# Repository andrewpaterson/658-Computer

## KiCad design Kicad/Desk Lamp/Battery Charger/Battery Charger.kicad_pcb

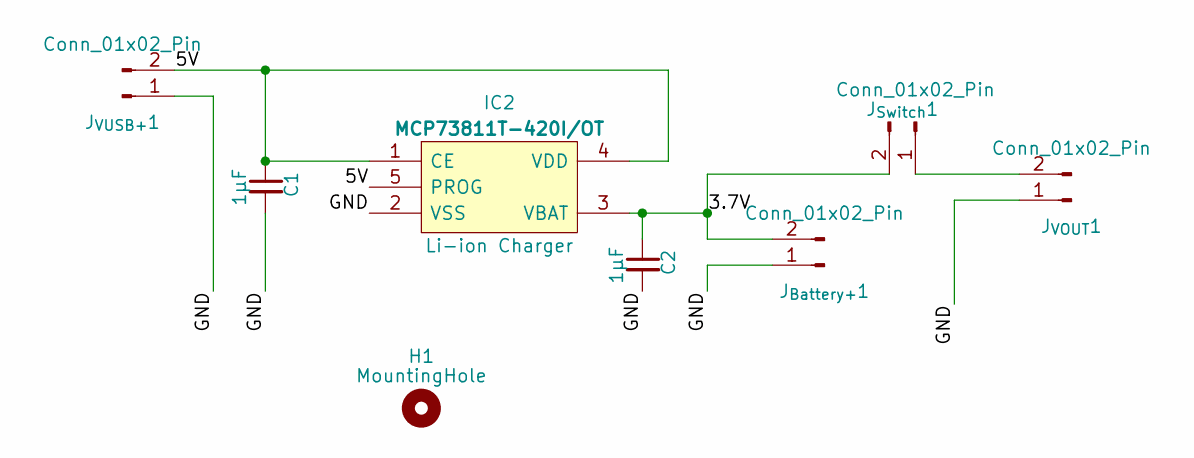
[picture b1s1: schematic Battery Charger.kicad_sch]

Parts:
C1, C2: 1μF; C_0805
H1: MountingHole; MountingHole_3.2mm_M3
IC2: MCP73811T-420I/OT; SOT95P270X145-5N; Manufacturer_Part_Number MCP73811T-420I/OT; Mouser Part Number 579-MCP73811T-420IOT
J_{Battery+}1: Conn_01x02_Pin; PinHeader_1x02_P2.54mm_Vertical
J_{Switch}1: Conn_01x02_Pin; PinHeader_1x02_P2.54mm_Vertical
J_{VOUT}1: Conn_01x02_Pin; PinHeader_1x02_P2.54mm_Vertical
J_{VUSB+}1: Conn_01x02_Pin; PinHeader_1x02_P2.54mm_Vertical

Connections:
/3.7V: C2.1, IC2.3 (VBAT), J_{Battery+}1.2, J_{Switch}1.2
/5V: C1.1, IC2.1 (CE), IC2.4 (VDD), IC2.5 (PROG), J_{VUSB+}1.2
/GND: C1.2, C2.2, IC2.2 (VSS), J_{Battery+}1.1, J_{VOUT}1.1, J_{VUSB+}1.1
unnamed: J_{Switch}1.1, J_{VOUT}1.2

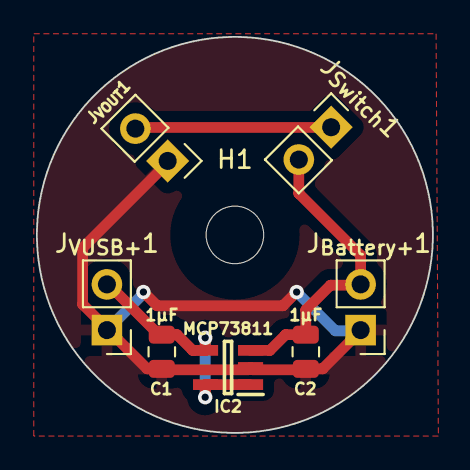
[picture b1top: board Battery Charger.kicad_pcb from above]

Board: 2 copper layers, 22.0 x 22.0 mm, 8 parts (0 on the bottom side), 4 nets.

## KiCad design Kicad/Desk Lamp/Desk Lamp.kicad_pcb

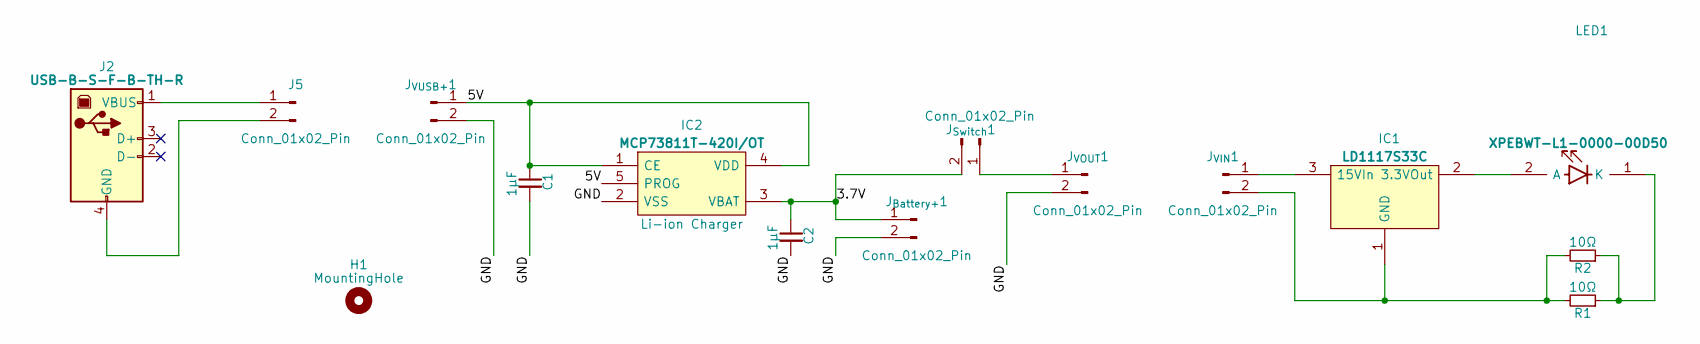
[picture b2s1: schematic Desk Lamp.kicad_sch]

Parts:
C1, C2: 1μF; C_0805
H1: MountingHole; MountingHole_3.2mm_M3
IC1: LD1117S33C; Manufacturer_Part_Number LD1117S33C
IC2: MCP73811T-420I/OT; SOT95P270X145-5N; Manufacturer_Part_Number MCP73811T-420I/OT; Mouser Part Number 579-MCP73811T-420IOT
J2: USB-B-S-F-B-TH-R; USBBSFBTHR; Manufacturer_Part_Number USB-B-S-F-B-TH-R; Mouser Part Number 200-USBBSFBTHR
J5: Conn_01x02_Pin; PinHeader_1x02_P2.54mm_Vertical
J_{Battery+}1: Conn_01x02_Pin; PinHeader_1x02_P2.54mm_Vertical
J_{Switch}1: Conn_01x02_Pin; PinHeader_1x02_P2.54mm_Vertical
J_{VIN}1: Conn_01x02_Pin; PinHeader_1x02_P2.54mm_Vertical
J_{VOUT}1: Conn_01x02_Pin; PinHeader_1x02_P2.54mm_Vertical
J_{VUSB+}1: Conn_01x02_Pin; PinHeader_1x02_P2.54mm_Vertical
LED1: XPEBWT-L1-0000-00D50; XPEBWTL1000000D50; Mouser Part Number 941-XPEBWTL1000D50
R1, R2: 10Ω; R_0805

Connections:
/3.7V: C2.1, IC2.3 (VBAT), J_{Battery+}1.1, J_{Switch}1.2
/5V: C1.1, IC2.1 (CE), IC2.4 (VDD), IC2.5 (PROG), J_{VUSB+}1.1
/GND: C1.2, C2.2, IC2.2 (VSS), J_{Battery+}1.2, J_{VOUT}1.2, J_{VUSB+}1.2
unnamed: IC1.2 (3.3VOut), LED1.2 (A)
unnamed: IC1.3 (15VIn), J_{VIN}1.1
unnamed: IC1.1 (GND), J_{VIN}1.2, R1.2, R2.2
unnamed: J2.4 (GND), J5.2
unnamed: J2.1 (VBUS), J5.1
unnamed: J_{Switch}1.1, J_{VOUT}1.1
unnamed: LED1.1 (K), R1.1, R2.1

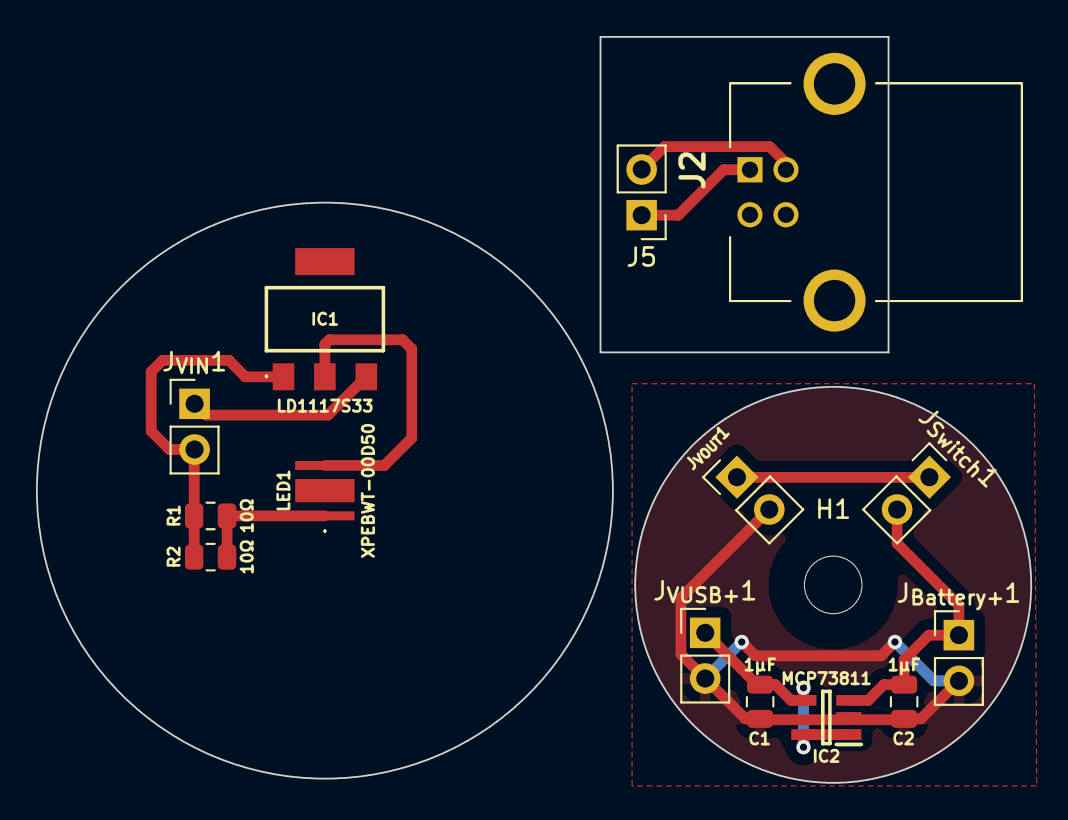
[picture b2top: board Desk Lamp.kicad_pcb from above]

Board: 2 copper layers, 55.2 x 41.4 mm, 15 parts (0 on the bottom side), 10 nets.

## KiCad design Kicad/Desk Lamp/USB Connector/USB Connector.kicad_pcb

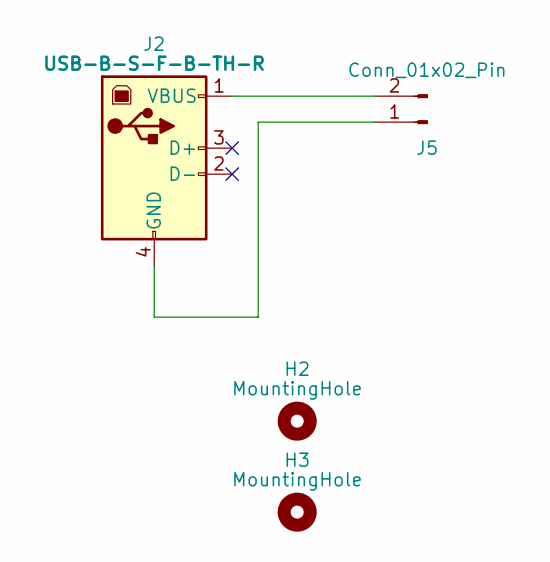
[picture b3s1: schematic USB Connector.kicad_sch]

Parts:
H2, H3: MountingHole; MountingHole_2.5mm
J2: USB-B-S-F-B-TH-R; USBBSFBTHR; Manufacturer_Part_Number USB-B-S-F-B-TH-R; Mouser Part Number 200-USBBSFBTHR
J5: Conn_01x02_Pin; PinHeader_1x02_P2.54mm_Vertical

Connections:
unnamed: J2.4 (GND), J5.1
unnamed: J2.1 (VBUS), J5.2

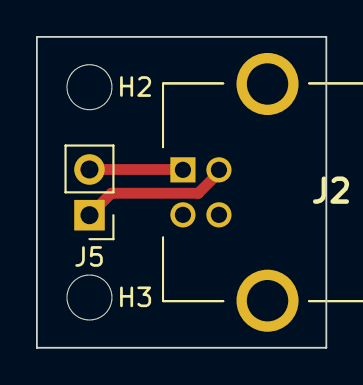
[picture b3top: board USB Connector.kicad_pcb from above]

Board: 2 copper layers, 16.1 x 17.3 mm, 4 parts (0 on the bottom side), 2 nets.

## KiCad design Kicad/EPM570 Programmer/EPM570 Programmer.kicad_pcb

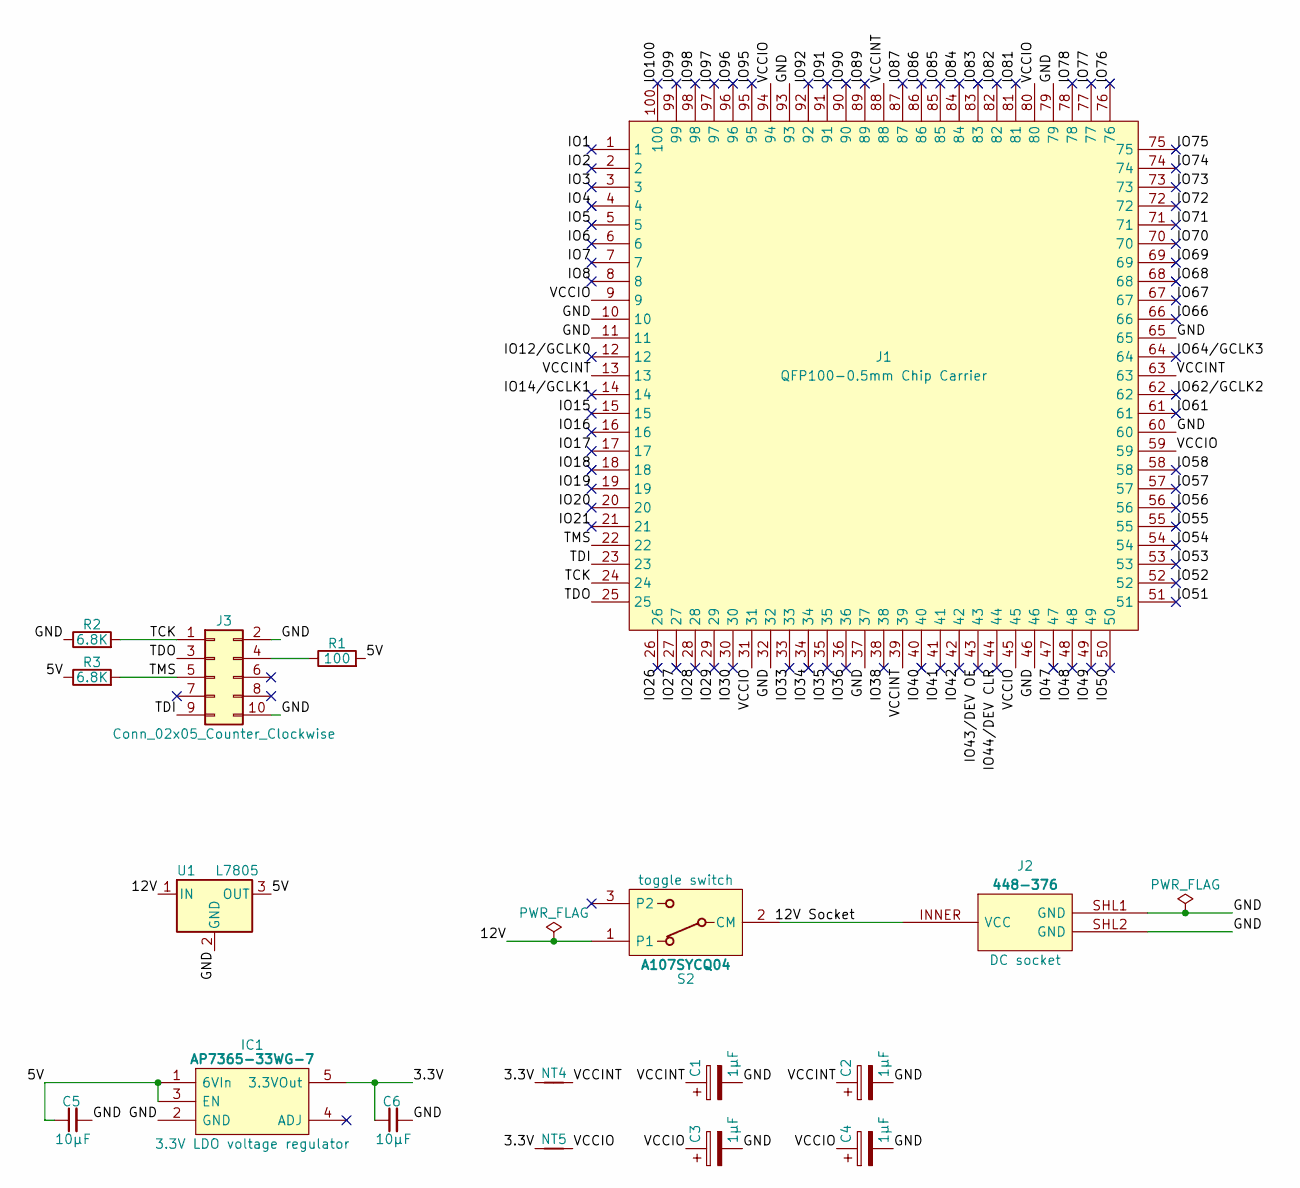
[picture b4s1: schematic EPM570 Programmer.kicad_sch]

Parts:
C1, C2, C3, C4: 1μF; CP_Radial_D4.0mm_P2.00mm
C5, C6: 10µF; C_0805
IC1: AP7365-33WG-7; SOT95P285X130-5N; Manufacturer_Part_Number AP7365-33WG-7; Mouser Part Number 621-AP7365-33WG-7
J1: AllSocket-QFP-100-14X14-0.5-Clamshell
J2: 448-376; 448376; Manufacturer_Part_Number 448-376
J3: Conn_02x05_Counter_Clockwise; PinHeader_2x05_P2.54mm_Vertical
NT4, NT5: NetTie_2; NetTie-2_SMD_Pad0.5mm
R1: 100; R_Axial_DIN0309_L9.0mm_D3.2mm_P12.70mm_Horizontal
R2, R3: 6.8K; R_Axial_DIN0207_L6.3mm_D2.5mm_P7.62mm_Horizontal
S2: A107SYCQ04; Manufacturer_Part_Number A107SYCQ04; Mouser Part Number 506-5-1825137-1
U1: L7805; TO-220-3_Vertical

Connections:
/3.3V: C6.1, IC1.5 (3.3VOut), NT4.1, NT5.1
/5V: C5.1, IC1.1 (6VIn), IC1.3 (EN), R1.2, R3.1, U1.3 (OUT)
/12V: S2.1, U1.1 (IN)
/12V Socket: J2.INNER (VCC), S2.2 (CM)
/GND: C1.2, C2.2, C3.2, C4.2, C5.2, C6.2, IC1.2 (GND), J1.10, J1.11, J1.32, J1.37, J1.46, J1.60, J1.65, J1.79, J1.93, J2.SHL1 (GND), J2.SHL2 (GND), J3.2, J3.10, R2.1, U1.2 (GND)
/IO1: J1.1
/IO2: J1.2
/IO3: J1.3
/IO4: J1.4
/IO5: J1.5
/IO6: J1.6
/IO7: J1.7
/IO8: J1.8
/IO12/GCLK0: J1.12
/IO14/GCLK1: J1.14
/IO15: J1.15
/IO16: J1.16
/IO17: J1.17
/IO18: J1.18
/IO19: J1.19
/IO20: J1.20
/IO21: J1.21
/IO26: J1.26
/IO27: J1.27
/IO28: J1.28
/IO29: J1.29
/IO30: J1.30
/IO33: J1.33
/IO34: J1.34
/IO35: J1.35
/IO36: J1.36
/IO38: J1.38
/IO40: J1.40
/IO41: J1.41
/IO42: J1.42
/IO43/DEV OE: J1.43
/IO44/DEV CLR: J1.44
/IO47: J1.47
/IO48: J1.48
/IO49: J1.49
/IO50: J1.50
/IO51: J1.51
/IO52: J1.52
/IO53: J1.53
/IO54: J1.54
/IO55: J1.55
/IO56: J1.56
/IO57: J1.57
/IO58: J1.58
/IO61: J1.61
/IO62/GCLK2: J1.62
/IO64/GCLK3: J1.64
/IO66: J1.66
/IO67: J1.67
/IO68: J1.68
/IO69: J1.69
/IO70: J1.70
/IO71: J1.71
/IO72: J1.72
/IO73: J1.73
/IO74: J1.74
/IO75: J1.75
/IO76: J1.76
/IO77: J1.77
/IO78: J1.78
/IO81: J1.81
/IO82: J1.82
/IO83: J1.83
/IO84: J1.84
/IO85: J1.85
/IO86: J1.86
/IO87: J1.87
/IO89: J1.89
/IO90: J1.90
/IO91: J1.91
/IO92: J1.92
/IO95: J1.95
/IO96: J1.96
/IO97: J1.97
/IO98: J1.98
/IO99: J1.99
/IO100: J1.100
/TCK: J1.24, J3.1, R2.2
/TDI: J1.23, J3.9
/TDO: J1.25, J3.3
/TMS: J1.22, J3.5, R3.2
/VCCINT: C1.1, C2.1, J1.13, J1.39, J1.63, J1.88, NT4.2
/VCCIO: C3.1, C4.1, J1.9, J1.31, J1.45, J1.59, J1.80, J1.94, NT5.2
unnamed: J3.4, R1.1

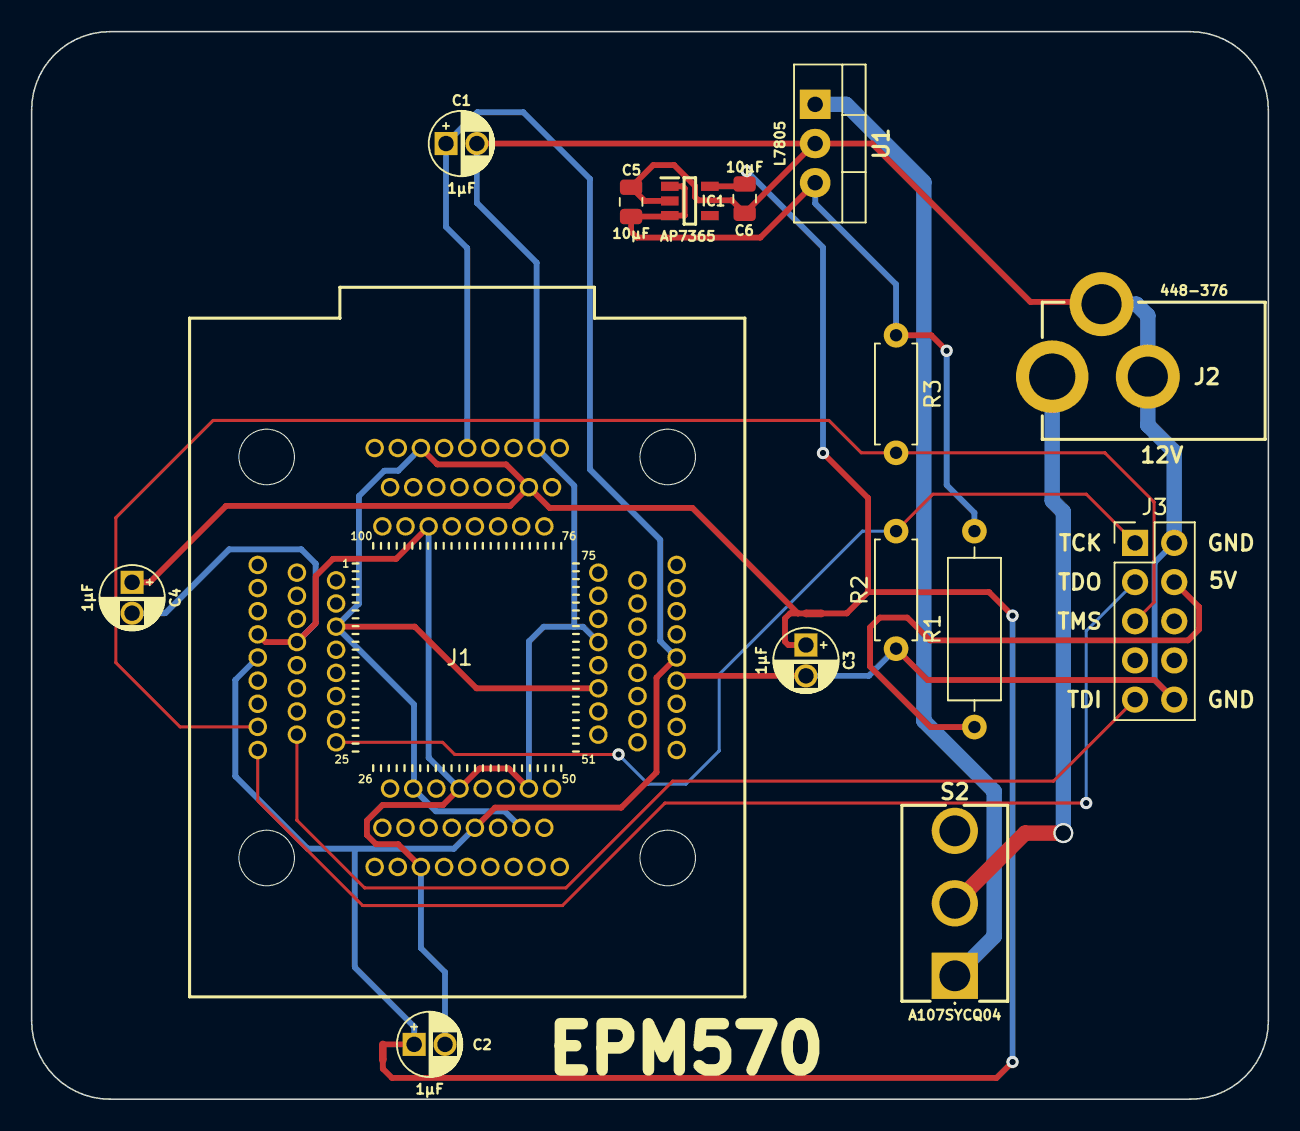
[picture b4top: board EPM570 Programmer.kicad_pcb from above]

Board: 2 copper layers, 80.2 x 69.2 mm, 17 parts (0 on the bottom side), 12 nets.

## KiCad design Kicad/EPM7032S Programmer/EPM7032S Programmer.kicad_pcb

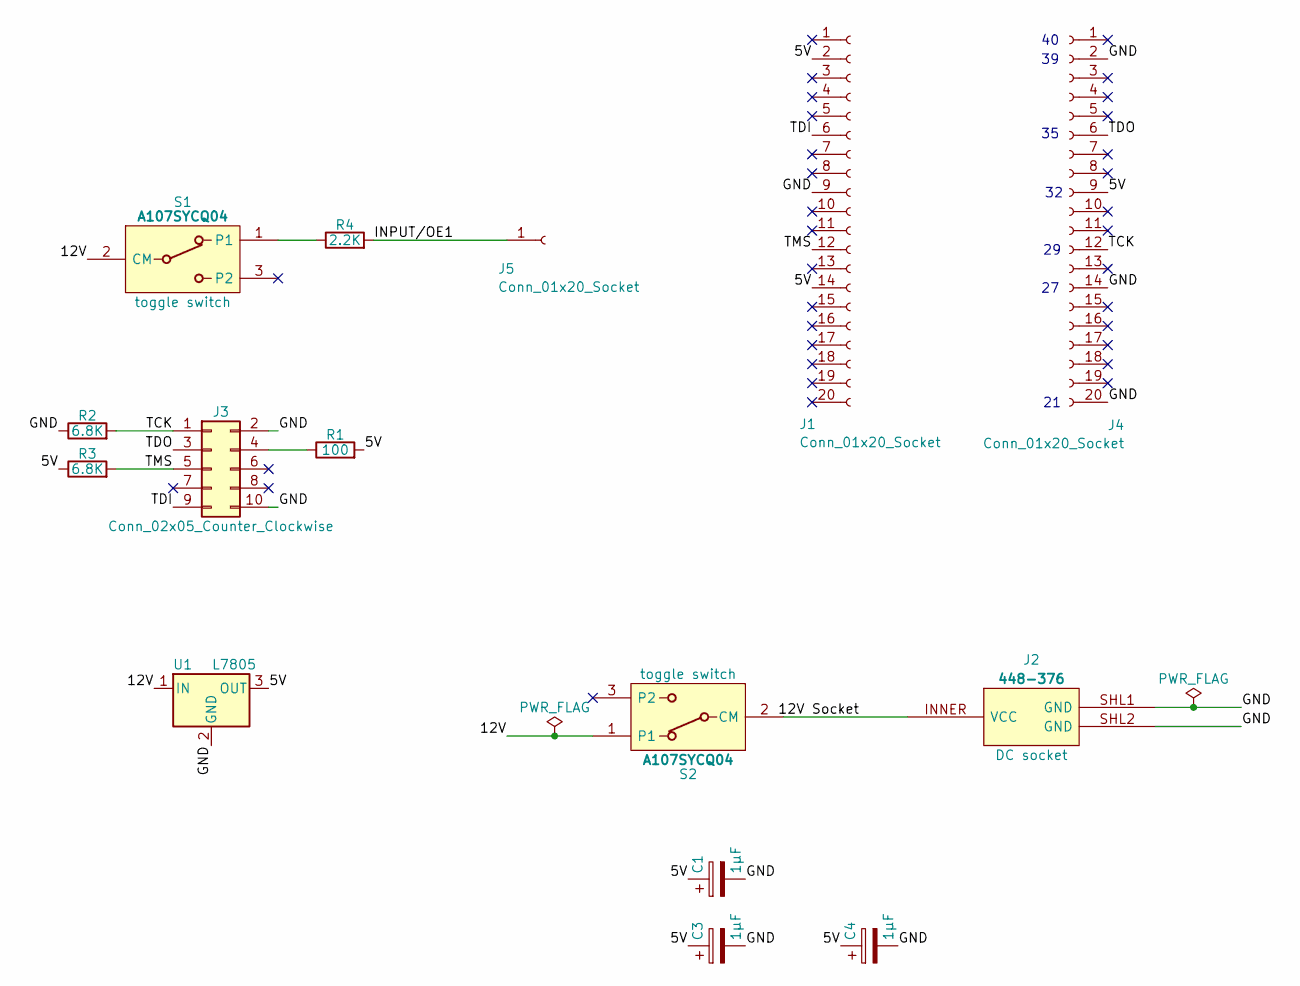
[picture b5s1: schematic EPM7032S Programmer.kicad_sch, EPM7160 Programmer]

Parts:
C1, C3, C4: 1μF; CP_Radial_D4.0mm_P2.00mm
J1, J4: Conn_01x20_Socket; PinSocket_1x20_P2.54mm_Vertical
J2: 448-376; 448376; Manufacturer_Part_Number 448-376
J3: Conn_02x05_Counter_Clockwise; PinHeader_2x05_P2.54mm_Vertical
J5: Conn_01x20_Socket; PinSocket_1x01_P2.54mm_Vertical
R1: 100; R_Axial_DIN0309_L9.0mm_D3.2mm_P12.70mm_Horizontal
R2, R3: 6.8K; R_Axial_DIN0207_L6.3mm_D2.5mm_P7.62mm_Horizontal
R4: 2.2K; R_Axial_DIN0207_L6.3mm_D2.5mm_P7.62mm_Horizontal
S1, S2: A107SYCQ04; Manufacturer_Part_Number A107SYCQ04; Mouser Part Number 506-5-1825137-1
U1: L7805; TO-220-3_Vertical

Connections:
/5V: C1.1, C3.1, C4.1, J1.2, J1.14, J4.9, R1.2, R3.1, U1.3 (OUT)
/12V: S1.2 (CM), S2.1, U1.1 (IN)
/12V Socket: J2.INNER (VCC), S2.2 (CM)
/GND: C1.2, C3.2, C4.2, J1.9, J2.SHL1 (GND), J2.SHL2 (GND), J3.2, J3.10, J4.2, J4.14, J4.20, R2.1, U1.2 (GND)
/INPUT/OE1: J5.1, R4.2
/TCK: J3.1, J4.12, R2.2
/TDI: J1.6, J3.9
/TDO: J3.3, J4.6
/TMS: J1.12, J3.5, R3.2
unnamed: J3.4, R1.1
unnamed: R4.1, S1.1

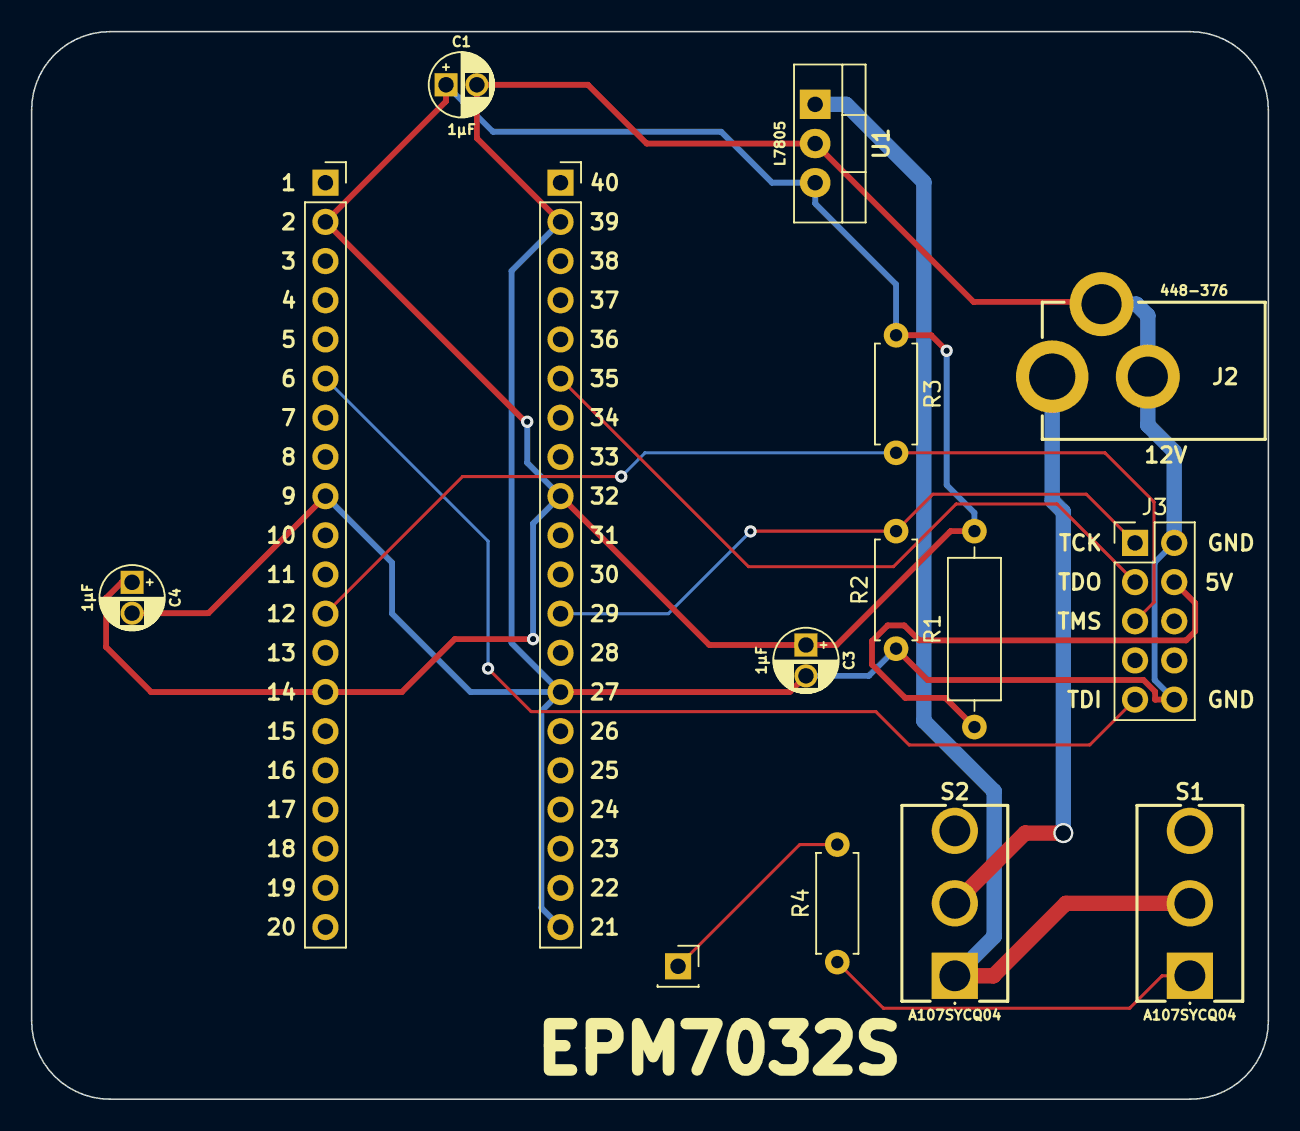
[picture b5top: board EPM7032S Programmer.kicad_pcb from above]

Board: 2 copper layers, 80.2 x 69.2 mm, 15 parts (0 on the bottom side), 11 nets.

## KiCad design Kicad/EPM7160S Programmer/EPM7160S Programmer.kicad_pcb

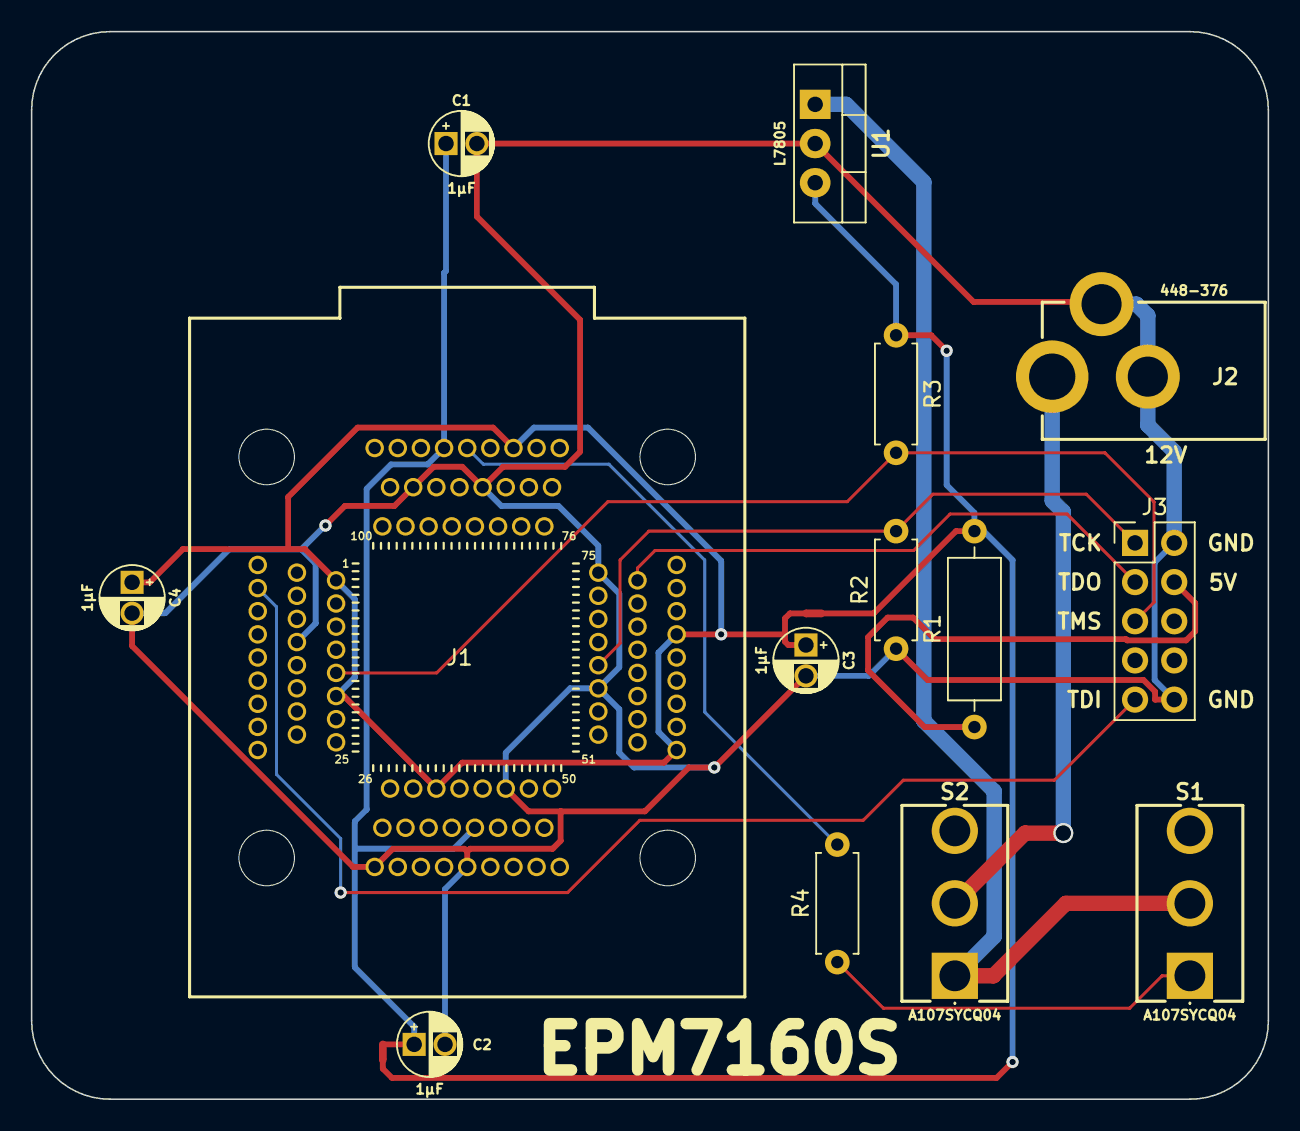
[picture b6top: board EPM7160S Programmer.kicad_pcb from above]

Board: 2 copper layers, 80.2 x 69.2 mm, 16 parts (0 on the bottom side), 13 nets.

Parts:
C1, C2, C3, C4: 1μF; CP_Radial_D4.0mm_P2.00mm
J1: AllSocket-QFP-100-14X14-0.5-Clamshell
J2: 448-376; 448376
J3: Conn_02x05_Counter_Clockwise; PinHeader_2x05_P2.54mm_Vertical
NT4, NT5: NetTie_2; NetTie-2_SMD_Pad0.5mm
R1: 100; R_Axial_DIN0309_L9.0mm_D3.2mm_P12.70mm_Horizontal
R2, R3: 6.8K; R_Axial_DIN0207_L6.3mm_D2.5mm_P7.62mm_Horizontal
R4: 2.2K; R_Axial_DIN0207_L6.3mm_D2.5mm_P7.62mm_Horizontal
S1, S2: A107SYCQ04
U1: L7805; TO-220-3_Vertical

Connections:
/5V: NT4.1, NT5.1, R1.2, R3.1, U1.3 (OUT)
/12V: S1.2 (CM), S2.1, U1.1 (IN)
/12V Socket: J2.INNER (VCC), S2.2 (CM)
/GND: C1.2, C2.2, C3.2, C4.2, J1.11, J1.26, J1.38, J1.43, J1.59, J1.74, J1.86, J1.95, J2.SHL1 (GND), J2.SHL2 (GND), J3.2, J3.10, R2.1, U1.2 (GND)
/INPUT/OE1: J1.88, R4.2
/TCK: J1.62, J3.1, R2.2
/TDI: J1.4, J3.9
/TDO: J1.73, J3.3
/TMS: J1.15, J3.5, R3.2
/VCCINT: C1.1, C2.1, J1.39, J1.91, NT4.2
/VCCIO: C3.1, C4.1, J1.3, J1.18, J1.34, J1.51, J1.66, J1.82, NT5.2
unnamed: J3.4, R1.1
unnamed: R4.1, S1.1

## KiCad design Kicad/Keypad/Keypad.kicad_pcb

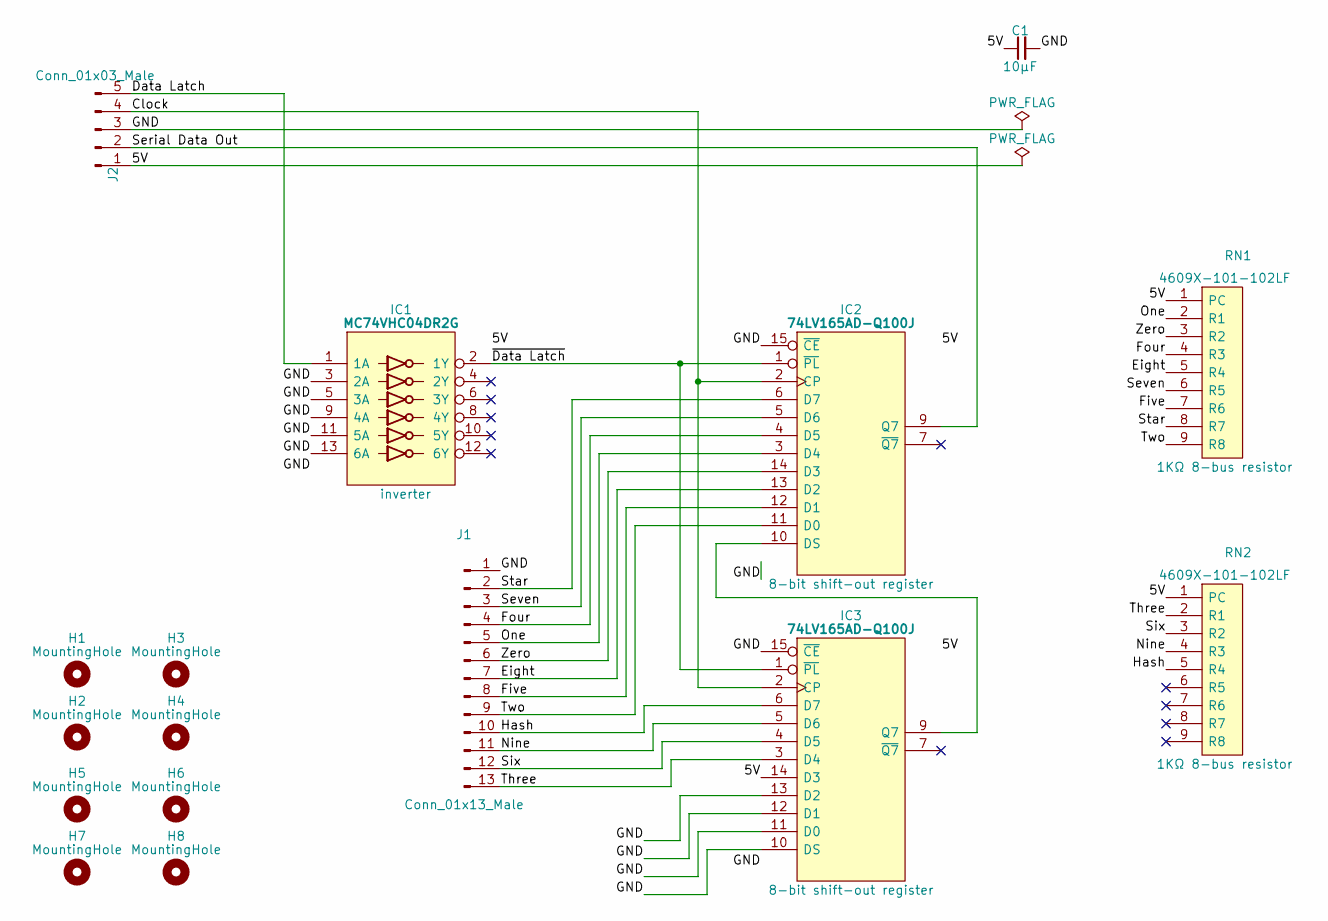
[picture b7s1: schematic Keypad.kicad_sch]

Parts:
C1: 10μF; C_0805
H1, H2, H3, H4: MountingHole; MountingHole_2.5mm
H5, H6, H7, H8: MountingHole; MountingHole_2mm
IC1: MC74VHC04DR2G; SOIC127P600X175-14N; Manufacturer_Part_Number MC74VHC04DR2G; Mouser Part Number 863-MC74VHC04DR2G
IC2, IC3: 74LV165AD-Q100J; SOIC127P600X175-16N; Mouser Part Number 771-74LV165ADQ100J
J1: Conn_01x13_Male; PinHeader_1x13_P2.54mm_Vertical
J2: Conn_01x03_Male; PinHeader_1x05_P2.54mm_Vertical
RN1, RN2: 4609X-101-102LF; 4609X; Manufacturer_Part_Number 4609X-101-102LF; Mouser Part Number 652-4609X-1LF-1K

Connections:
/5V: C1.1, IC1.14 (5V), IC2.16 (VCC), IC3.14 (D3), IC3.16 (VCC), J2.1, RN1.1 (PC), RN2.1 (PC)
/Clock: IC2.2 (CP), IC3.2 (CP), J2.4
/Data Latch: IC1.1 (1A), J2.5
/Eight: IC2.13 (D2), J1.7, RN1.5 (R4)
/Five: IC2.12 (D1), J1.8, RN1.7 (R6)
/Four: IC2.4 (D5), J1.4, RN1.4 (R3)
/GND: C1.2, IC1.3 (2A), IC1.5 (3A), IC1.7 (GND), IC1.9 (4A), IC1.11 (5A), IC1.13 (6A), IC2.8 (GND), IC2.15 (~CE), IC3.8 (GND), IC3.10 (DS), IC3.11 (D0), IC3.12 (D1), IC3.13 (D2), IC3.15 (~CE), J1.1, J2.3
/Hash: IC3.6 (D7), J1.10, RN2.5 (R4)
/Nine: IC3.5 (D6), J1.11, RN2.4 (R3)
/One: IC2.3 (D4), J1.5, RN1.2 (R1)
/Serial Data Out: IC2.9 (Q7), J2.2
/Seven: IC2.5 (D6), J1.3, RN1.6 (R5)
/Six: IC3.4 (D5), J1.12, RN2.3 (R2)
/Star: IC2.6 (D7), J1.2, RN1.8 (R7)
/Three: IC3.3 (D4), J1.13, RN2.2 (R1)
/Two: IC2.11 (D0), J1.9, RN1.9 (R8)
/Zero: IC2.14 (D3), J1.6, RN1.3 (R2)
/~Data Latch: IC1.2 (1Y), IC2.1 (~PL), IC3.1 (~PL)
unnamed: IC2.10 (DS), IC3.9 (Q7)

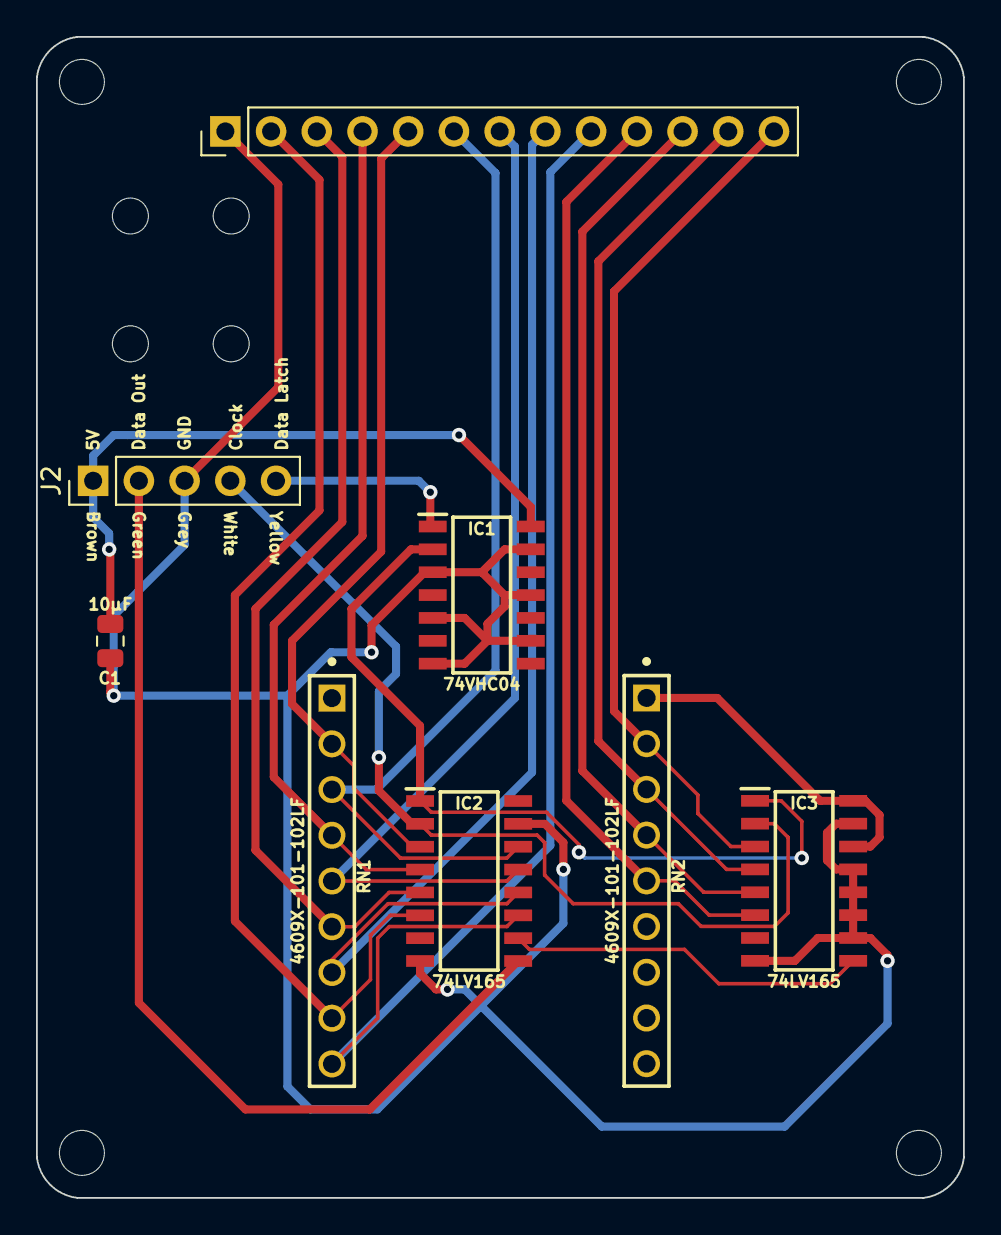
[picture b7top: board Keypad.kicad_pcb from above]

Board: 2 copper layers, 51.5 x 64.5 mm, 16 parts (0 on the bottom side), 19 nets.
